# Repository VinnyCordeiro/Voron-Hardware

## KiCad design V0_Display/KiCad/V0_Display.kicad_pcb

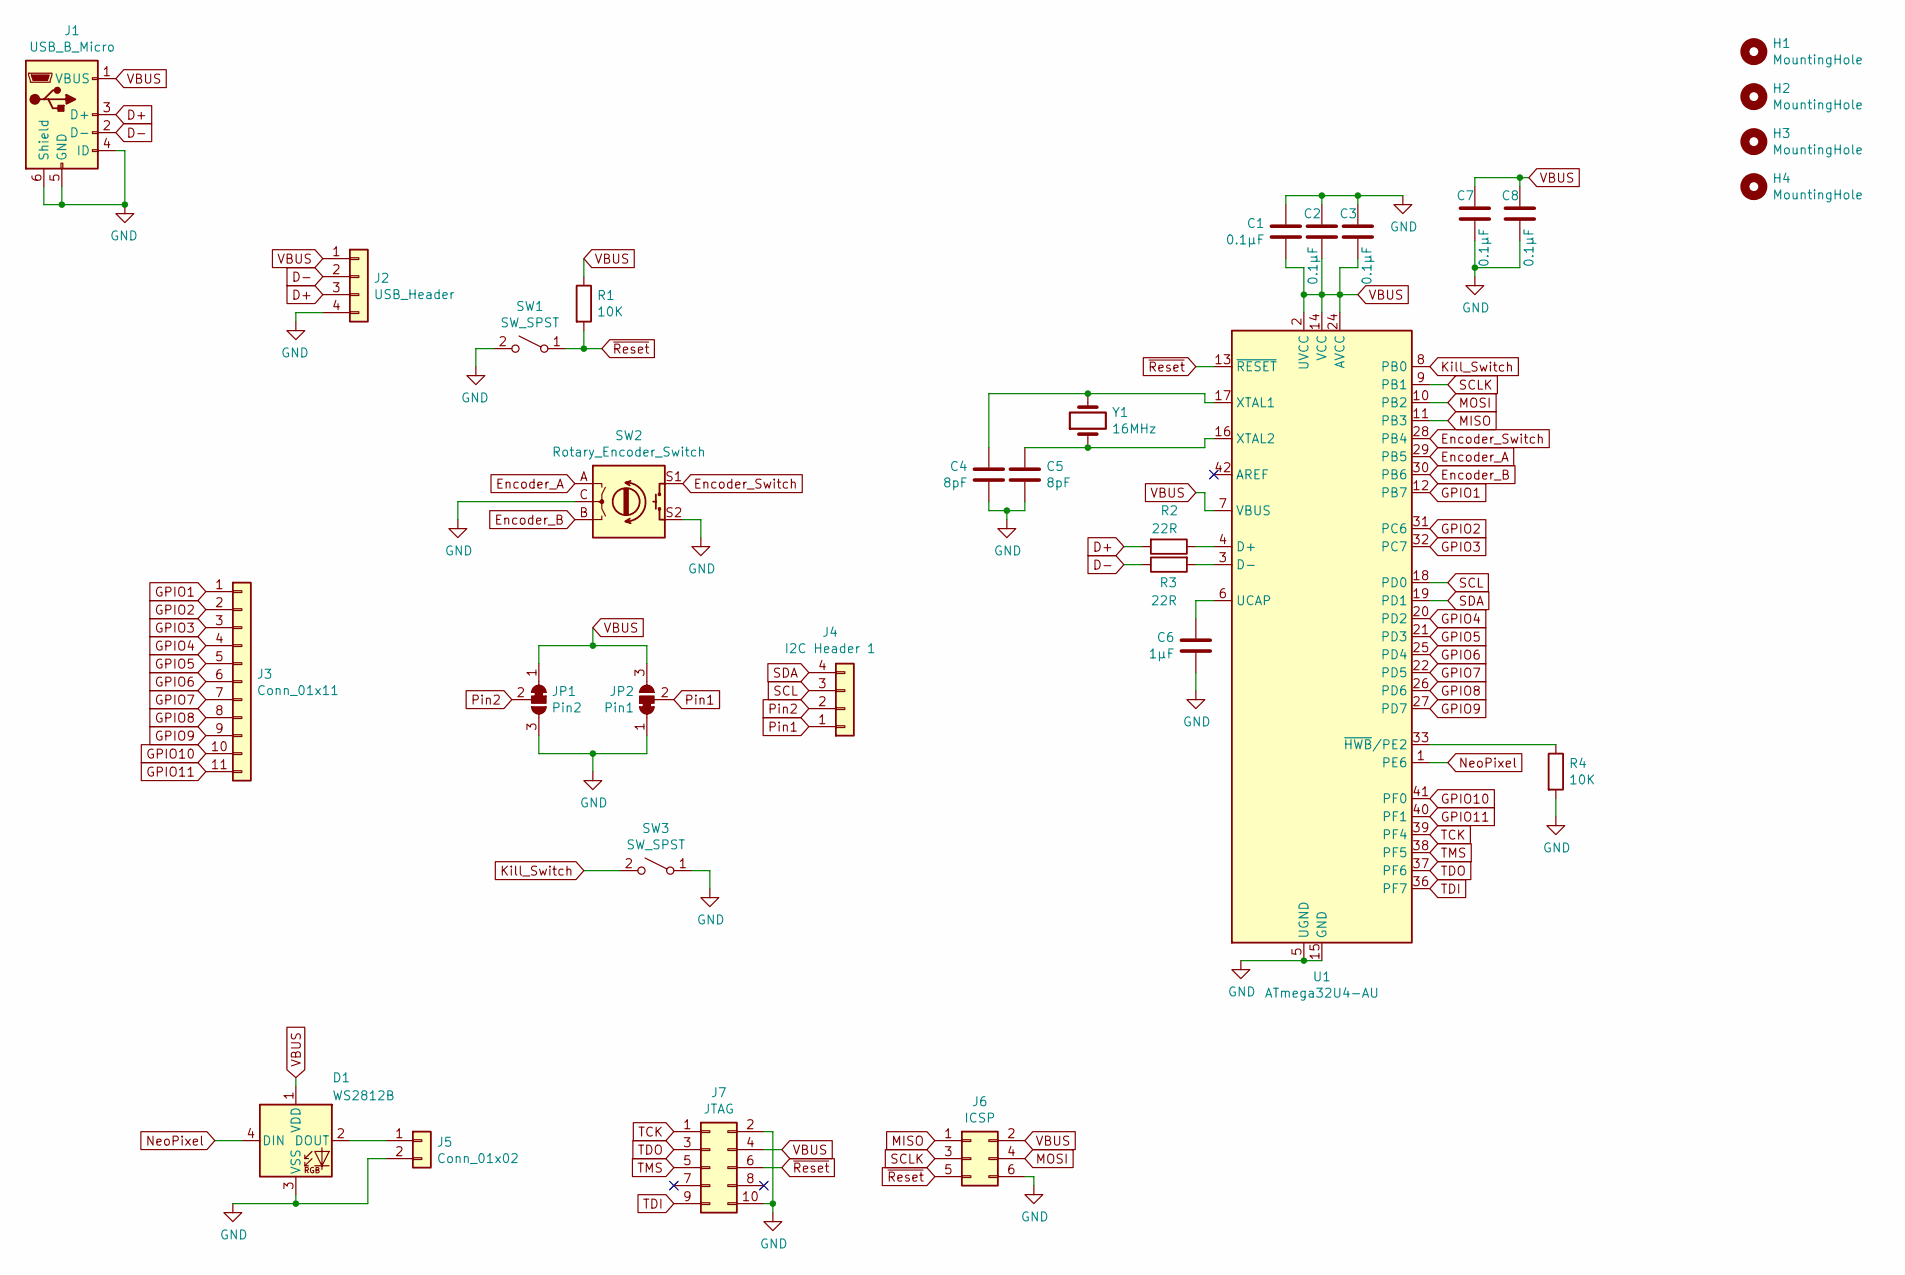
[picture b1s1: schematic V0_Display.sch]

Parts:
C1, C2, C3, C7, C8: 0.1µF; C_0805_2012Metric; LCSC C49678
C4, C5: 8pF; C_0805_2012Metric; LCSC C1779
C6: 1µF; C_0805_2012Metric; LCSC C49678
D1: WS2812B; LED_WS2812B_PLCC4_5.0x5.0mm_P3.2mm
H1, H2, H3, H4: MountingHole; MountingHole_3.2mm_M3
J1: USB_B_Micro; MolexVertical&Horizontal_MicroB
J2: USB_Header; PinHeader_1x04_P2.54mm_Vertical
J3: Conn_01x11; Pin_Header_Straight_1x11_Pitch2.54mm
J4: I2C Header 1; 1pt3in_OLED
J5: Conn_01x02; PinHeader_1x02_P2.54mm_Vertical
J6: ICSP; Pin_Header_Straight_2x03_Pitch2.54mm
J7: JTAG; Pin_Header_Straight_2x05_Pitch1.27mm
JP1: Pin2; SolderJumper-3_P1.3mm_Bridged12_Pad1.0x1.5mm
JP2: Pin1; SolderJumper-3_P1.3mm_Bridged12_Pad1.0x1.5mm
R1, R4: 10K; R_0805_2012Metric; LCSC C17414
R2, R3: 22R; R_0805_2012Metric; LCSC C17414
SW1, SW3: SW_SPST; SW_PUSH_6mm
SW2: Rotary_Encoder_Switch; EN11_Encoder
U1: ATmega32U4-AU; TQFP-44_10x10mm_Pitch0.8mm
Y1: 16MHz; Crystal_HC50_Vertical

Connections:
D+: J1.3 (D+), J2.3, R2.2
D-: J1.2 (D-), J2.2, R3.1
Encoder_A: SW2.A, U1.29 (PB5)
Encoder_B: SW2.B, U1.30 (PB6)
Encoder_Switch: SW2.S1, U1.28 (PB4)
GND: C1.1, C2.1, C3.1, C4.2, C5.2, C6.2, C7.2, C8.2, D1.3 (VSS), J1.4 (ID), J1.5 (GND), J1.6 (Shield), J2.4, J5.2, J6.6, J7.2, J7.10, JP1.3 (B), JP2.1 (A), R4.2, SW1.2 (B), SW2.C, SW2.S2, SW3.1 (A), U1.5 (UGND), U1.15 (GND), U1.23 (GND), U1.35 (GND), U1.43 (GND)
GPIO1: J3.1, U1.12 (PB7)
GPIO2: J3.2, U1.31 (PC6)
GPIO3: J3.3, U1.32 (PC7)
GPIO4: J3.4, U1.20 (PD2)
GPIO5: J3.5, U1.21 (PD3)
GPIO6: J3.6, U1.25 (PD4)
GPIO7: J3.7, U1.22 (PD5)
GPIO8: J3.8, U1.26 (PD6)
GPIO9: J3.9, U1.27 (PD7)
GPIO10: J3.10, U1.41 (PF0)
GPIO11: J3.11, U1.40 (PF1)
Kill_Switch: SW3.2 (B), U1.8 (PB0)
MISO: J6.1, U1.11 (PB3)
MOSI: J6.4, U1.10 (PB2)
NeoPixel: D1.4 (DIN), U1.1 (PE6)
unnamed: C4.1, U1.17 (XTAL1), Y1.2
unnamed: C5.1, U1.16 (XTAL2), Y1.1
unnamed: C6.1, U1.6 (UCAP)
unnamed: D1.2 (DOUT), J5.1
unnamed: R2.1, U1.4 (D+)
unnamed: R3.2, U1.3 (D-)
unnamed: R4.1, U1.33 (~HWB~/PE2)
Pin1: J4.1, JP2.2 (C)
Pin2: J4.2, JP1.2 (C)
SCL: J4.3, U1.18 (PD0)
SCLK: J6.3, U1.9 (PB1)
SDA: J4.4, U1.19 (PD1)
TCK: J7.1, U1.39 (PF4)
TDI: J7.9, U1.36 (PF7)
TDO: J7.3, U1.37 (PF6)
TMS: J7.5, U1.38 (PF5)
VBUS: C1.2, C2.2, C3.2, C7.1, C8.1, D1.1 (VDD), J1.1 (VBUS), J2.1, J6.2, J7.4, JP1.1 (A), JP2.3 (B), R1.1, U1.2 (UVCC), U1.7 (VBUS), U1.14 (VCC), U1.24 (AVCC), U1.34 (VCC), U1.44 (AVCC)
~Reset: J6.5, J7.6, R1.2, SW1.1 (A), U1.13 (~RESET)

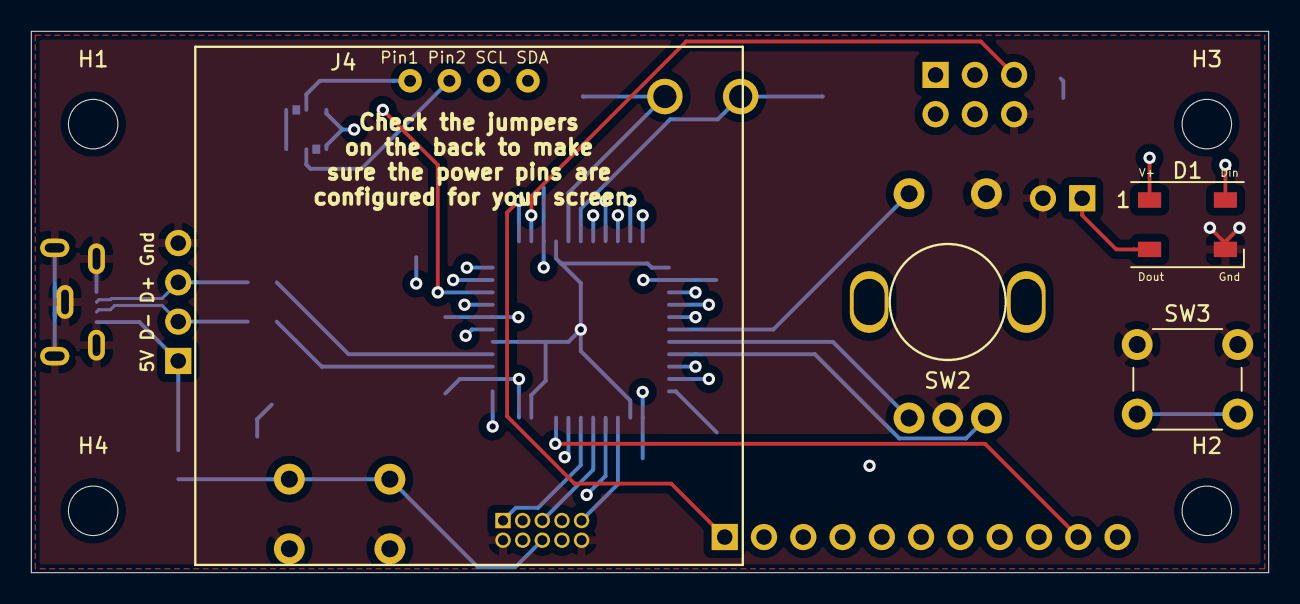
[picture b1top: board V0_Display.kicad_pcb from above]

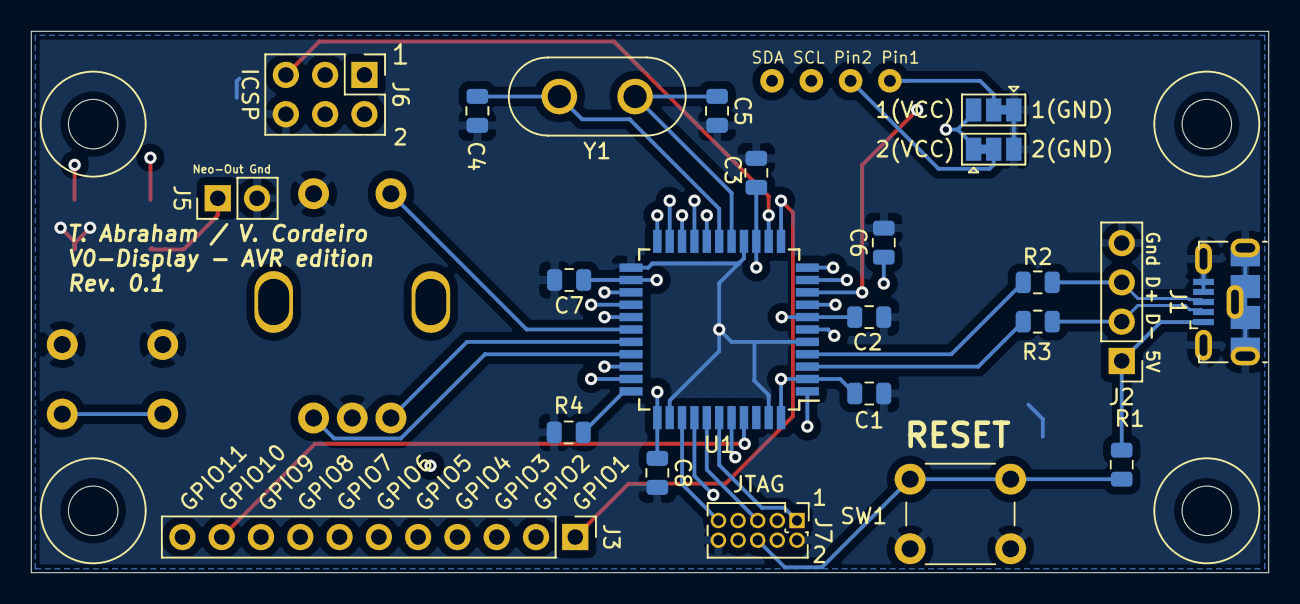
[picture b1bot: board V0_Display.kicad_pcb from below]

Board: 4 copper layers, 80.0 x 35.0 mm, 31 parts (23 on the bottom side), 39 nets.

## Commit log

2021-03-08 Microcontroller change
    Changed the STM32F042 microcontroller for an ATmega32U4, given the scarcity of the former due to the pandemic of Covid-19.
2021-03-08 Microcontroller change - gerbers
    Changed the original STM32F042 microcontroller for an ATmega32U4. Production files.
